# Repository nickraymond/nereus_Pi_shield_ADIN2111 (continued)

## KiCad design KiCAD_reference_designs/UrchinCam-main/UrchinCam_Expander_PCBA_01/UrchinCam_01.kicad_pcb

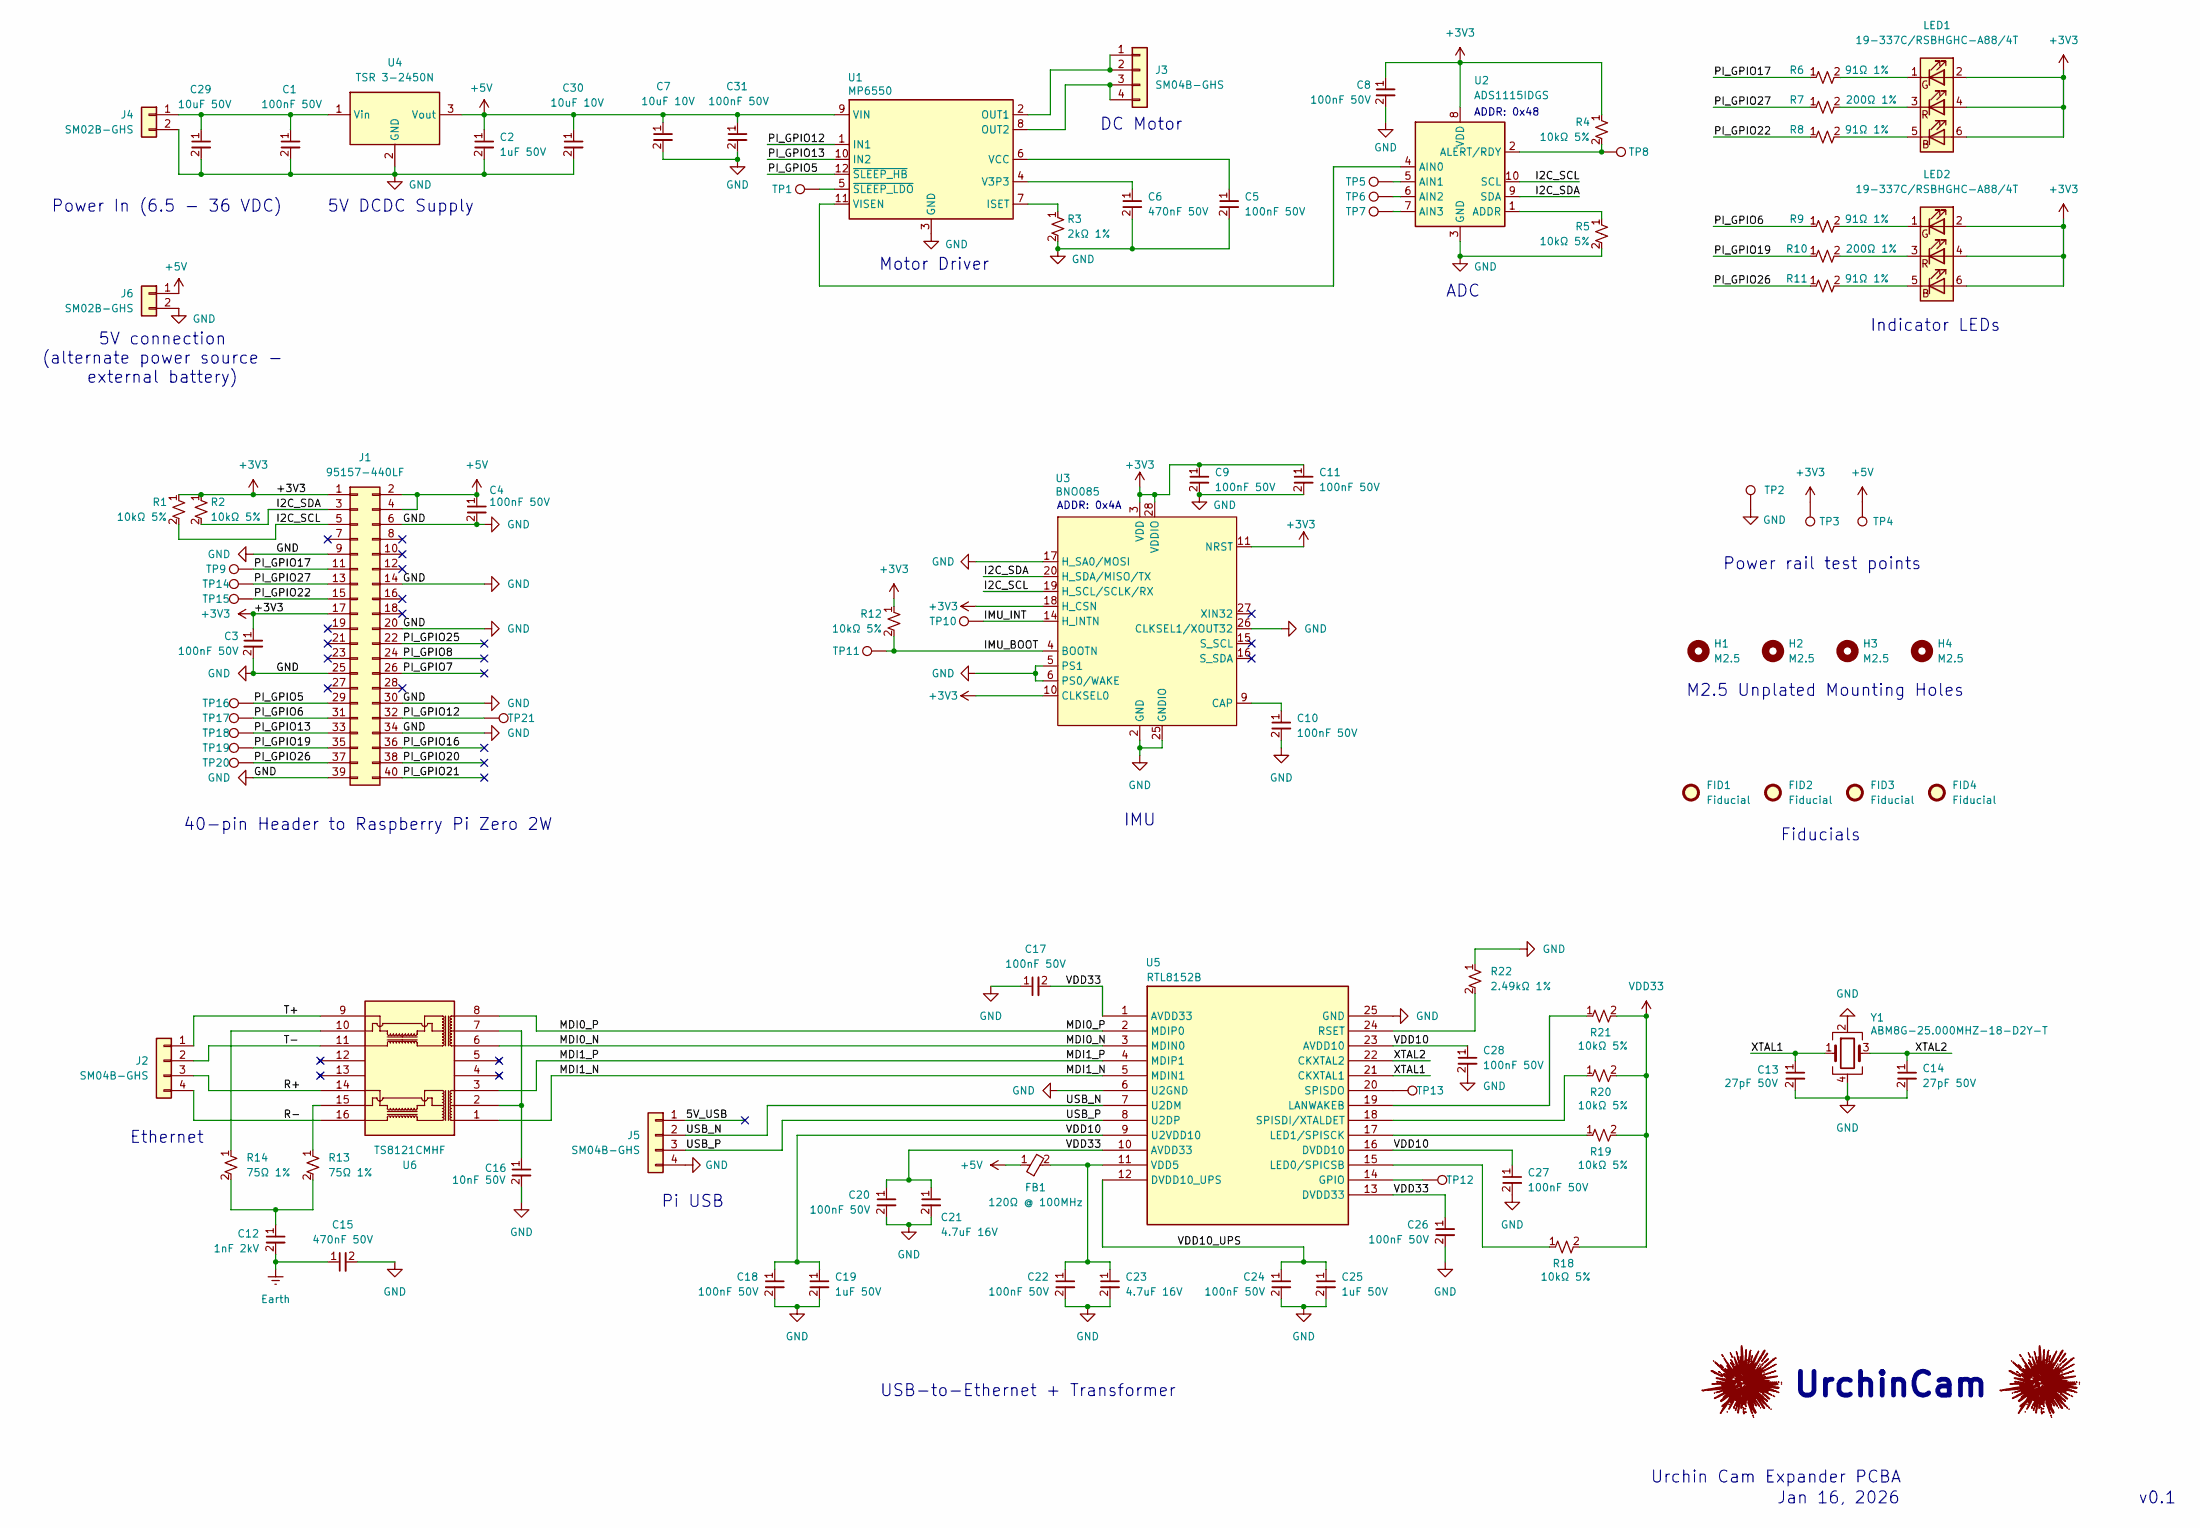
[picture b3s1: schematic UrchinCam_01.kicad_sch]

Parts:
C1, C3, C4, C5, C8, C9, C10, C11, C17, C18, C20, C22, C24, C26, C27, C28, C31: 100nF 50V; C_0402_1005Metric_Pad0.74x0.62mm_HandSolder
C2, C19, C25: 1uF 50V; C_0402_1005Metric_Pad0.74x0.62mm_HandSolder
C6, C15: 470nF 50V; C_0402_1005Metric_Pad0.74x0.62mm_HandSolder
C7, C30: 10uF 10V; C_0402_1005Metric_Pad0.74x0.62mm_HandSolder
C12: 1nF 2kV; C_1206_3216Metric_Pad1.33x1.80mm_HandSolder
C13, C14: 27pF 50V; C_0402_1005Metric_Pad0.74x0.62mm_HandSolder
C16: 10nF 50V; C_0402_1005Metric_Pad0.74x0.62mm_HandSolder
C21, C23: 4.7uF 16V; C_0402_1005Metric_Pad0.74x0.62mm_HandSolder
C29: 10uF 50V; C_0805_2012Metric_Pad1.18x1.45mm_HandSolder
FB1: 120Ω @ 100MHz; R_0402_1005Metric_Pad0.72x0.64mm_HandSolder
FID1, FID2, FID3, FID4: Fiducial; Fiducial_0.5mm_Mask1mm
H1, H2, H3, H4: M2.5; M2.5_Mounting_Hole_2.9mm_unplated
J1: 95157-440LF; Amphenol_95157-440LF_2x20_P2.54mm_Vertical
J2, J3, J5: SM04B-GHS; JST_GH_SM04B-GHS-TB_1x04-1MP_P1.25mm_Horizontal
J4, J6: SM02B-GHS; JST_GH_SM02B-GHS-TB_1x02-1MP_P1.25mm_Horizontal
LED1, LED2: 19-337C/RSBHGHC-A88/4T; 19-337C RSBHGHC-A88 4T
R1, R2, R4, R5, R12, R18, R19, R20, R21: 10kΩ 5%; R_0402_1005Metric_Pad0.72x0.64mm_HandSolder
R3: 2kΩ 1%; R_0402_1005Metric_Pad0.72x0.64mm_HandSolder
R6, R8, R9, R11: 91Ω 1%; R_0603_1608Metric_Pad0.98x0.95mm_HandSolder
R7, R10: 200Ω 1%; R_0603_1608Metric_Pad0.98x0.95mm_HandSolder
R13, R14: 75Ω 1%; R_0402_1005Metric_Pad0.72x0.64mm_HandSolder
R22: 2.49kΩ 1%; R_0402_1005Metric_Pad0.72x0.64mm_HandSolder
TP1, TP2, TP3, TP4, TP5, TP6, TP7, TP8, TP9, TP10, TP11, TP12, TP13, TP14, TP15, TP16, TP17, TP18, TP19, TP20, TP21: TestPoint; TestPoint_Pad_D1.5mm
U1: MP6550; MP6550GG
U2: ADS1115IDGS; TSSOP-10_3x3mm_P0.5mm
U3: BNO085; LGA-28_5.2x3.8mm_P0.5mm
U4: TSR 3-2450N; Traco_TSR 3-2450N
U5: RTL8152B
U6: TS8121CMHF; TS8121CM HF
Y1: ABM8G-25.000MHZ-18-D2Y-T; Crystal_SMD_3225-4Pin_3.2x2.5mm

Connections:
+3V3: C3.1, C8.1, C9.1, C11.1, J1.1, J1.17, LED1.2 (GA), LED1.4 (RA), LED1.6 (BA), LED2.2 (GA), LED2.4 (RA), LED2.6 (BA), R1.1, R2.1, R4.1, R12.1, TP3.1, U2.8 (VDD), U3.3 (VDD), U3.10 (CLKSEL0), U3.11 (NRST), U3.18 (H_CSN), U3.28 (VDDIO)
+5V: C2.1, C4.1, C7.1, C30.1, C31.1, FB1.1, J1.2, J1.4, J6.1, TP4.1, U1.9 (VIN), U4.3 (Vout)
/5V_USB: J5.1
/I2C_SCL: J1.5, R1.2, U2.10 (SCL), U3.19 (H_SCL/SCLK/RX)
/I2C_SDA: J1.3, R2.2, U2.9 (SDA), U3.20 (H_SDA/MISO/TX)
/IMU_BOOT: R12.2, TP11.1, U3.4 (BOOTN)
/IMU_INT: TP10.1, U3.14 (H_INTN)
/MDI0_N: U5.3 (MDIN0), U6.6
/MDI0_P: U5.2 (MDIP0), U6.8
/MDI1_N: U5.5 (MDIN1), U6.1
/MDI1_P: U5.4 (MDIP1), U6.3
/PI_GPIO5: J1.29, TP16.1, U1.12 (~SLEEP_HB)
/PI_GPIO6: J1.31, R9.1, TP17.1
/PI_GPIO7: J1.26
/PI_GPIO8: J1.24
/PI_GPIO12: J1.32, TP21.1, U1.1 (IN1)
/PI_GPIO13: J1.33, TP18.1, U1.10 (IN2)
/PI_GPIO16: J1.36
/PI_GPIO17: J1.11, R6.1, TP9.1
/PI_GPIO19: J1.35, R10.1, TP19.1
/PI_GPIO20: J1.38
/PI_GPIO21: J1.40
/PI_GPIO22: J1.15, R8.1, TP15.1
/PI_GPIO25: J1.22
/PI_GPIO26: J1.37, R11.1, TP20.1
/PI_GPIO27: J1.13, R7.1, TP14.1
/R+: J2.3, U6.14
/R-: J2.4, U6.16
/T+: J2.1, U6.9
/T-: J2.2, U6.11
/USB_N: J5.2, U5.7 (U2DM)
/USB_P: J5.3, U5.8 (U2DP)
/VDD10: C18.1, C19.1, C27.1, C28.1, U5.9 (U2VDD10), U5.16 (DVDD10), U5.23 (AVDD10)
/VDD10_UPS: C24.1, C25.1, U5.12 (DVDD10_UPS)
/XTAL1: C13.1, U5.21 (CKXTAL1), Y1.1
/XTAL2: C14.1, U5.22 (CKXTAL2), Y1.3
Earth: C12.2, C15.1
GND: C1.2, C2.2, C3.2, C4.2, C5.2, C6.2, C7.2, C8.2, C9.2, C10.2, C11.2, C13.2, C14.2, C15.2, C16.2, C17.1, C18.2, C19.2, C20.2, C21.2, C22.2, C23.2, C24.2, C25.2, C26.2, C27.2, C28.2, C29.2, C30.2, C31.2, J1.6, J1.9, J1.14, J1.20, J1.25, J1.30, J1.34, J1.39, J4.2, J5.4, J6.2, R3.2, R5.2, R22.1, TP2.1, U1.3 (GND), U2.3 (GND), U3.2 (GND), U3.5 (PS1), U3.6 (PS0/WAKE), U3.17 (H_SA0/MOSI), U3.25 (GNDIO), U3.26 (CLKSEL1/XOUT32), U4.2 (GND), U5.6 (U2GND), U5.25 (GND), Y1.2, Y1.4
unnamed: C12.1, R13.2, R14.2
unnamed: C16.1, U6.2, U6.7
unnamed: J3.1, J3.2, U1.2 (OUT1)
unnamed: J3.3, J3.4, U1.8 (OUT2)
unnamed: C1.1, C29.1, J4.1, U4.1 (Vin)
unnamed: LED1.5 (BK), R8.2
unnamed: LED1.1 (GK), R6.2
unnamed: LED1.3 (RK), R7.2
unnamed: LED2.5 (BK), R11.2
unnamed: LED2.1 (GK), R9.2
unnamed: LED2.3 (RK), R10.2
unnamed: R13.1, U6.15
unnamed: R14.1, U6.10
unnamed: R3.1, U1.7 (ISET)
unnamed: C6.1, U1.4 (V3P3)
unnamed: C5.1, U1.6 (VCC)
unnamed: U1.11 (VISEN), U2.4 (AIN0)
unnamed: TP1.1, U1.5 (~SLEEP_LDO)
unnamed: R5.1, U2.1 (ADDR)
unnamed: TP5.1, U2.5 (AIN1)
unnamed: TP6.1, U2.6 (AIN2)
unnamed: TP7.1, U2.7 (AIN3)
unnamed: R4.2, TP8.1, U2.2 (ALERT/RDY)
unnamed: C10.1, U3.9 (CAP)
unnamed: TP12.1, U5.14 (GPIO)
unnamed: R21.1, U5.19 (LANWAKEB)
unnamed: R18.1, U5.15 (LED0/SPICSB)
unnamed: R19.1, U5.17 (LED1/SPISCK)
unnamed: R22.2, U5.24 (RSET)
unnamed: R20.1, U5.18 (SPISDI/XTALDET)
unnamed: TP13.1, U5.20 (SPISDO)
unnamed: C22.1, C23.1, FB1.2, U5.11 (VDD5)
VDD33: C17.2, C20.1, C21.1, C26.1, R18.2, R19.2, R20.2, R21.2, U5.1 (AVDD33), U5.10 (AVDD33), U5.13 (DVDD33)

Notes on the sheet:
Ethernet
Power In (6.5 - 36 VDC)
Motor Driver
UrchinCam
Urchin Cam Expander PCBA
Power rail test points
DC Motor
ADC
M2.5 Unplated Mounting Holes
Pi USB
v0.1
IMU
Indicator LEDs
Jan 16, 2026
ADDR: 0x48
5V connection (alternate power source - external battery)
Fiducials
40-pin Header to Raspberry Pi Zero 2W
USB-to-Ethernet + Transformer
ADDR: 0x4A
5V DCDC Supply

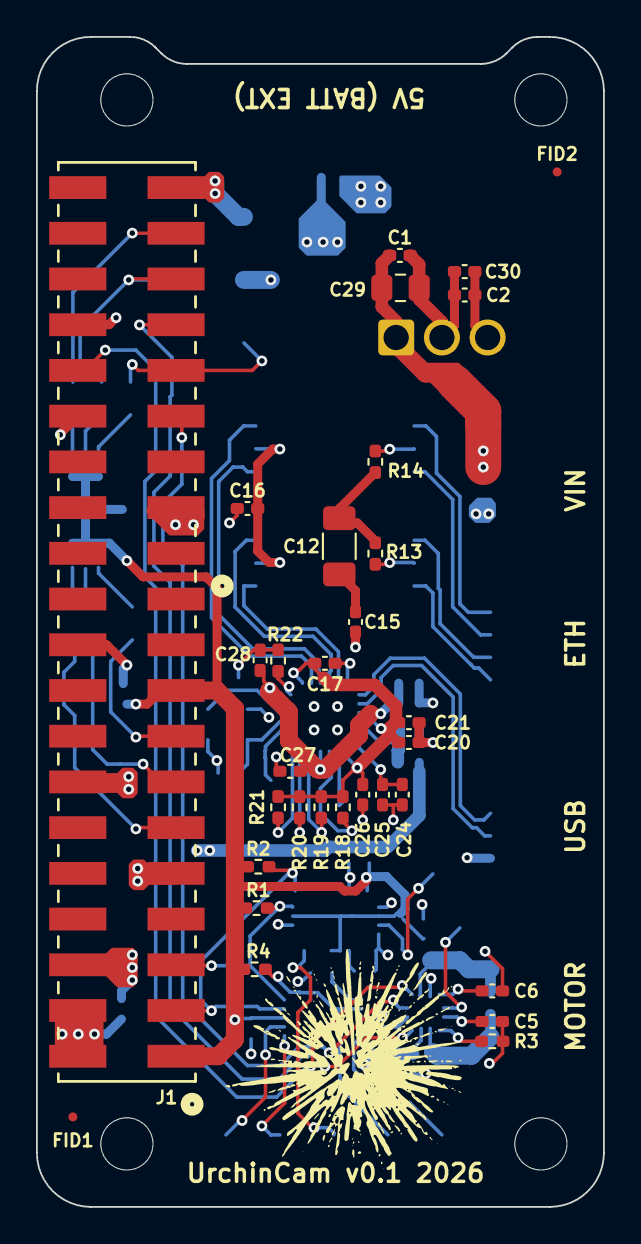
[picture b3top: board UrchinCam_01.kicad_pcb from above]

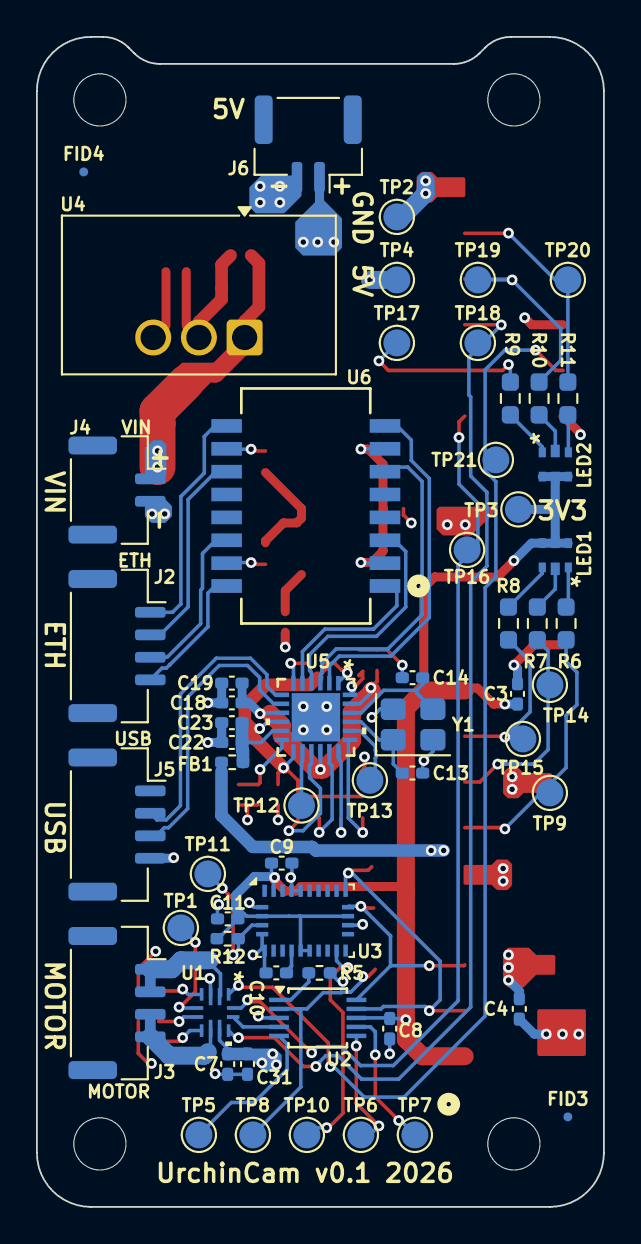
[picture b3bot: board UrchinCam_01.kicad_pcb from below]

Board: 4 copper layers, 31.5 x 65.0 mm, 95 parts (60 on the bottom side), 64 nets.

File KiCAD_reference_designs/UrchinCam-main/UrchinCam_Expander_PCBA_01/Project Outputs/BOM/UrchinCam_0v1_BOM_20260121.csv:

Id,Comment,Designator,Footprint,Quantity,Manufacturer 1,Manufacturer Part Number 1,JLPCB Part Number
1,SM02B-GHS,"J6,J4",JST_GH_SM02B-GHS-TB_1x02-1MP_P1.25mm_Horizontal,2,JST,SM02B-GHS,C189893
2,10uF 50V,C29,C_0805_2012Metric_Pad1.18x1.45mm_HandSolder,1,Murata,GRM21BR61H106KE43L,C440198
3,10uF 10V,"C30,C7",C_0402_1005Metric_Pad0.74x0.62mm_HandSolder,2,Murata,GRM155R61A106ME11D,C408132
4,100nF 50V,"C1,C28,C5,C27,C24,C26,C17,C20,C22,C11,C8,C10,C9,C3,C18,C31,C4",C_0402_1005Metric_Pad0.74x0.62mm_HandSolder,17,Yageo,CC0402KRX5R9BB104,C105882
5,1uF 50V,"C2,C25,C19",C_0402_1005Metric_Pad0.74x0.62mm_HandSolder,3,Taiyo Yuden,UMK105CBJ105MV-F,C2880413
6,TSR 3-2450N,U4,Traco_TSR 3-2450N,1,Traco Power,TSR 3-2450N,C42463890
7,MP6550,U1,MP6550GG,1,Monolithic Power Systems Inc.,MP6550GG,C3681248
8,RTL8152B,U5,RTL8152B,1,Realtek,RTL8152B,C50656
9,2kΩ 1%,R3,R_0402_1005Metric_Pad0.72x0.64mm_HandSolder,1,Vishay Dale,CRCW04022K00FKED,C482125
10,10kΩ 5%,"R2,R21,R19,R1,R18,R20,R4,R5,R12",R_0402_1005Metric_Pad0.72x0.64mm_HandSolder,9,Yageo,RC0402JR-0710KL,C60489
12,75Ω 1%,"R14,R13",R_0402_1005Metric_Pad0.72x0.64mm_HandSolder,2,Yageo,RC0402FR-0775RL,C114757
13,4.7uF 16V,"C21,C23",C_0402_1005Metric_Pad0.74x0.62mm_HandSolder,2,Samsung Electro-Mechanics,CL05A475MO5NUNC,C318563
14,1nF 2kV,C12,C_1206_3216Metric_Pad1.33x1.80mm_HandSolder,1,Samsung Electro-Mechanics,CL31B102KJHNNNE,C16196254
15,470nF 50V,"C15,C6",C_0402_1005Metric_Pad0.74x0.62mm_HandSolder,2,Taiyo Yuden,UMK105ABJ474KV-F,C386109
16,95157-440LF,J1,Amphenol_95157-440LF_2x20_P2.54mm_Vertical,1,Amphenol ICC (FCI),95157-440LF,C5411221
17,10nF 50V,C16,C_0402_1005Metric_Pad0.74x0.62mm_HandSolder,1,Yageo,CC0402KRX7R9BB103,C60133
18,2.49kΩ 1%,R22,R_0402_1005Metric_Pad0.72x0.64mm_HandSolder,1,Vishay Dale,CRCW04022K49FKED,C482132
19,SM04B-GHS,"J2,J3,J5",JST_GH_SM04B-GHS-TB_1x04-1MP_P1.25mm_Horizontal,3,JST,SM04B-GHS,C189895
21,ADS1115IDGS,U2,TSSOP-10_3x3mm_P0.5mm,1,Texas Instruments,ADS1115IDGS,C468683
22,120Ω @ 100MHz,FB1,R_0402_1005Metric_Pad0.72x0.64mm_HandSolder,1,Murata,BLM15PD121SN1D,C76891
23,27pF 50V,"C14,C13",C_0402_1005Metric_Pad0.74x0.62mm_HandSolder,2,Murata,GRM1555C1H270JA01J,C3892269
24,200Ω 1%,"R10,R7",R_0603_1608Metric_Pad0.98x0.95mm_HandSolder,2,Vishay Dale,CRCW0603200RFKEA,C844754
25,91Ω 1%,"R8,R9,R11,R6",R_0603_1608Metric_Pad0.98x0.95mm_HandSolder,4,Yageo,RC0603FR-0791RL,C137670
26,ABM8G-25.000MHZ-18-D2Y-T,Y1,Crystal_SMD_3225-4Pin_3.2x2.5mm,1,Abracon LLC,ABM8G-25.000MHZ-18-D2Y-T,C2939753
27,TS8121CMHF,U6,TS8121CM HF,1,Pulse Electronics,TS8121CM HF,C5718404
28,BNO085,U3,LGA-28_5.2x3.8mm_P0.5mm,1,"CEVA Technologies, Inc.",BNO085,C5189642
29,19-337C/RSBHGHC-A88/4T,"LED2,LED1",19-337C RSBHGHC-A88 4T,2,Everlight Electronics Co Ltd,19-337C/RSBHGHC-A88/4T,C3019536

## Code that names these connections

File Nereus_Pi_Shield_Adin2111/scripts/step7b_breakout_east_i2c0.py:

"""Step 7b and step 5 (I2C0): the six east breakout nets and I2C0 with its pull-ups.

East breakout, J1 pin -> J2 pin, 0.2 mm, no via:
  top layer   (north -> south)  MOTOR_IN2 82.65 | MOTOR_IN1 83.10 | MOTOR_nSLEEP 83.55
  Internal 2  (north -> south)  SPI1_SCLK 82.90 | SPI1_MOSI 83.40 | SPI1_MISO 83.90
  SPI1_SCLK passes east of J2 to reach pin 23; its lane stays 3.3 mm from H2 (keep-out radius 3.0 mm).

I2C0: Sofar's two top stubs end at (159.25 / 159.75, 99.63), walled in by INT on the top layer. Each gets a small
via (0.45 / 0.2 mm, beside the SPI vias of the same size) and continues on an inner layer: SCL on Internal 1,
SDA on Internal 2. North through J2's pin gap at x 159.21 to J1 pins 28 / 27; east below J2 to J2 pins 16 / 15.

R26 / R27 (4.7 k pull-ups to PI_3V3) sat on old 3V3 copper of the mote, which shorted 3V3 to PI_3V3. They move
below J2 beside pin 13 (PI_3V3) and pin 15 (SDA). One 0.6 / 0.3 mm via brings SCL up to R26. The 1.47 mm of
old 3V3 track that joined their former pads is removed.
"""
import sys
import pcbnew
import boardio
from boardio import add_track, add_via, find_tracks, pad_xy, place

b = boardio.load()
fp = boardio.footprints(b)
tracks = list(b.GetTracks())
if any(t.GetNetname().endswith("MOTOR_IN1") for t in tracks):
    sys.exit("step 7b already applied (MOTOR_IN1 has copper); nothing done")
P = 1.27
j1 = lambda n: pad_xy(b, "J1", n)
j2 = lambda n: pad_xy(b, "J2", n)
ROW = (j1("1")[1] + j1("2")[1]) / 2
BOT_ROW, GAP_IN, GAP_OUT = j1("1")[1], 84.00, 86.37

def lane(pin, gap_x, lane_y):
    x, y = j1(pin)
    if abs(y - BOT_ROW) < 0.01:
        return [(x, y), (x, lane_y - 0.60), (x + 0.60, lane_y)]
    return [(x, y), (gap_x, ROW), (gap_x, lane_y - 1.00), (gap_x + 1.00, lane_y)]

def south_pin(pin, lane_y):
    """Leave the lane into the J2 pin gap west of a south-row pin, then 45 degrees into the pin."""
    x, y = j2(pin)
    g = x - P
    return [(g - (GAP_IN - lane_y), lane_y), (g, GAP_IN), (g, GAP_OUT), (x, y)]

def north_pin(pin, lane_y, run=0.45):
    x, y = j2(pin)
    return [(x - run, lane_y), (x, lane_y + run), (x, y)]

L = {}
# ---- east breakout, top
L["MOTOR_nSLEEP"] = add_track(b, "MOTOR_nSLEEP", "Top Layer", lane("29", None, 83.55) + south_pin("17", 83.55))
L["MOTOR_IN1"] = add_track(b, "MOTOR_IN1", "Top Layer", lane("32", j1("31")[0] - P, 83.10) + south_pin("19", 83.10))
L["MOTOR_IN2"] = add_track(b, "MOTOR_IN2", "Top Layer", lane("33", None, 82.65) + north_pin("20", 82.65))
# ---- east breakout, Internal 2
L["SPI1_MISO"] = add_track(b, "SPI1_MISO", "Internal 2", lane("35", None, 83.90) + south_pin("21", 83.90))
L["SPI1_MOSI"] = add_track(b, "SPI1_MOSI", "Internal 2", lane("38", j1("37")[0] + P, 83.40) + north_pin("24", 83.40, 0.50))
xe = j2("24")[0] + P + 0.07                                       # x 179.60: east of J2
L["SPI1_SCLK"] = add_track(b, "SPI1_SCLK", "Internal 2",
    lane("40", j1("39")[0] + P, 82.90) + [(xe - 0.70, 82.90), (xe, 83.60), (xe, j2("23")[1] - 0.70), (xe - 0.70, j2("23")[1]), j2("23")])

# ---- I2C0
GX = j2("8")[0] + P                                               # x 159.21: the J2 pin gap used by INT on top
add_via(b, "I2C0_SCL", 159.25, 91.70, 0.45, 0.2)
add_via(b, "I2C0_SDA", 159.75, 92.60, 0.45, 0.2)
L["I2C0_SCL"] = add_track(b, "I2C0_SCL", "Top Layer", [(159.25, 99.63), (159.25, 91.70)])
L["I2C0_SDA"] = add_track(b, "I2C0_SDA", "Top Layer", [(159.75, 99.63), (159.75, 92.60)])
g28 = j1("27")[0] + P                                             # x 158.96: J1 pin gap for pin 28
L["I2C0_SCL"] += add_track(b, "I2C0_SCL", "Internal 1",
    [(159.25, 91.70), (GX, 91.20), (GX, 83.20), (g28, 82.95), (g28, ROW), j1("28")])
g16 = j2("16")[0] + P                                             # x 169.37
L["I2C0_SCL"] += add_track(b, "I2C0_SCL", "Internal 1",
    [(GX, 91.20), (g16 - 1.00, 91.20), (g16, 90.20), (g16, GAP_OUT), j2("16")])
L["I2C0_SDA"] += add_track(b, "I2C0_SDA", "Internal 2",
    [(159.75, 92.60), (159.75, 90.60), (GX, 90.06), (GX, 83.50), (j1("27")[0], 81.98), j1("27")])
L["I2C0_SDA"] += add_track(b, "I2C0_SDA", "Internal 2",
    [(159.75, 90.60), (j2("15")[0] - 1.10, 90.60), (j2("15")[0], 89.50), j2("15")])

# ---- R26 / R27 below J2
old_3v3 = find_tracks(b, tracks, "3V3", "Top Layer", (147.2, 108.3, 149.1, 108.8))
assert len(old_3v3) == 1, len(old_3v3)
p13, p15 = j2("13"), j2("15")
place(fp["R27"], 166.83, 89.40, {"2": (166.43, 89.40), "1": (167.23, 89.40)})
place(fp["R26"], p13[0], 90.60, {"2": (p13[0], 90.20), "1": (p13[0], 91.00)})
L["PI_3V3"] = add_track(b, "PI_3V3", "Top Layer", [(166.43, 89.40), (165.95, 88.92), (p13[0] + 0.30, 88.30)])
L["PI_3V3"] += add_track(b, "PI_3V3", "Top Layer", [(p13[0], 90.20), (p13[0], 88.30)])
L["I2C0_SDA"] += add_track(b, "I2C0_SDA", "Top Layer", [(167.23, 89.40), (167.71, 88.92), (p15[0] - 0.30, 88.30)])
add_via(b, "I2C0_SCL", p13[0], 91.85)
L["I2C0_SCL"] += add_track(b, "I2C0_SCL", "Top Layer", [(p13[0], 91.00), (p13[0], 91.85)])
L["I2C0_SCL"] += add_track(b, "I2C0_SCL", "Internal 1", [(p13[0], 91.85), (p13[0], 91.20)])

for t in old_3v3:
    b.Remove(t)
boardio.save(b)
for n, v in L.items():
    print("  %-13s %.2f mm added" % (n, v))
boardio.report(["R26", "R27"])
